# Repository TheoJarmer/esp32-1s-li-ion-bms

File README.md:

# ESP32 1S Li-ion BMS & Power Board

2-layer KiCad PCB that charges and protects a single Li-ion cell and
provides a regulated 3.3V rail for an ESP32.

## Features
- USB-C input, charging via TP4056 (R_PROG = 2 kOhm, about 600 mA from the datasheet formula, not measured)
- Cell protection (DW01A + FS8205A)
- Automatic USB/battery power-path switching (P-MOSFET Q2 + Schottky D4)
- 3.3V regulation (AP2112K-3.3)

## Power path
USB power feeds the 3.3V regulator through Schottky diode D4, and P-channel
MOSFET Q2 (gate tied to VBUS) connects the battery to the same node only when
USB is absent. D4 blocks current flowing back to the USB port.

## Testing done
- 3.3V output from USB power
- 3.3V output from battery power
- 3.3V output maintained when switching between USB and battery (unplugging each at different times)
- Battery charging

## Not tested
- Operation with an ESP32 connected
- Measured charge current
- Protection cutoffs (overcurrent, over-discharge, short circuit)
- Temperature sensing (TH1 replaced by a fixed 10 kOhm resistor on the built board)

## Files
- hardware/: KiCad project
- manufacturing/: gerbers, bom.csv, jlcpcb_order_bom.csv, placement file
- docs/: schematic PDF
- img/: photos and PCB render

## Build
5 boards fabricated by JLCPCB (SMD parts assembled by JLCPCB, through-hole parts hand-soldered).
Designed and simulated in KiCad 10.0.

## License
MIT

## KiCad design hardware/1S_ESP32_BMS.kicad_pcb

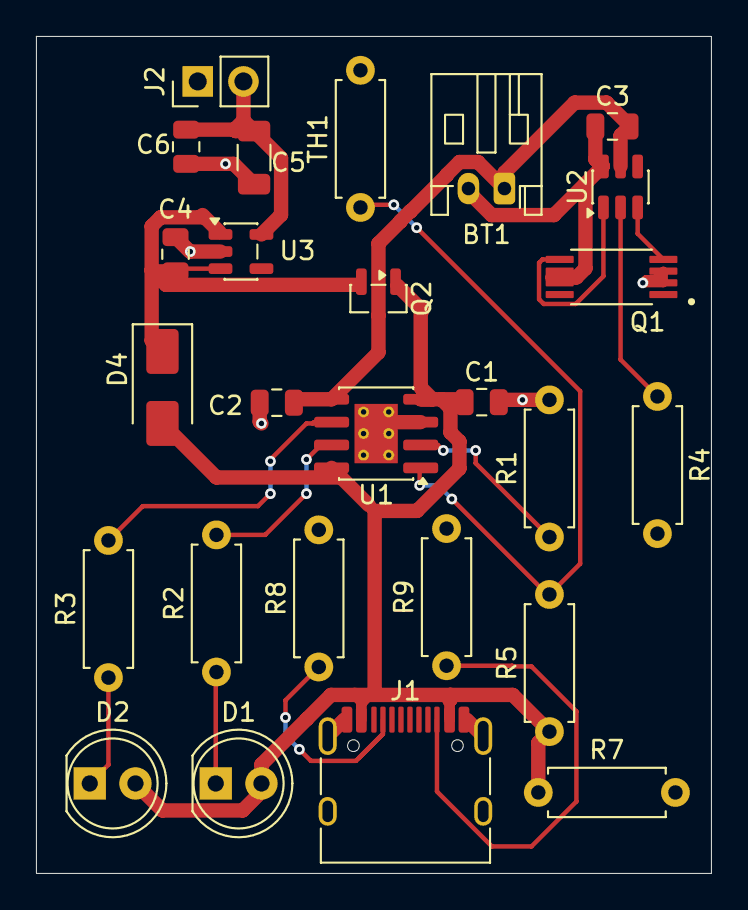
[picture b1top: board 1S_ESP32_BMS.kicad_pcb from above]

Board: 2 copper layers, 37.5 x 46.5 mm, 26 parts (0 on the bottom side), 17 nets.

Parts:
BT1: Battery_Cell; JST_PH_S2B-PH-K_1x02_P2.00mm_Horizontal
C1, C4: 10 uf; C_0805_2012Metric
C2: 10uf; C_0805_2012Metric
C3: 0.1uf; C_0805_2012Metric
C5: 22 uf; C_1206_3216Metric
C6: 0.1 uf; C_0805_2012Metric
D1: RED LED; LED_D5.0mm
D2: Green LED; LED_D5.0mm
D4: SS14; D_SMA
J1: USB_C_Receptacle_PowerOnly_24P; USB_C_Receptacle_HRO_TYPE-C-31-M-12
J2: Conn_01x02_Pin; PinHeader_1x02_P2.54mm_Vertical
Q1: FS8205A; SOP65P640X120-8N
Q2: AO3401A; SOT-23
R1: 4.7 kohm; R_Axial_DIN0207_L6.3mm_D2.5mm_P7.62mm_Horizontal
R2, R3, R4: 1kohm; R_Axial_DIN0207_L6.3mm_D2.5mm_P7.62mm_Horizontal
R5: 10 kmohm; R_Axial_DIN0207_L6.3mm_D2.5mm_P7.62mm_Horizontal
R7: 100 kmohm; R_Axial_DIN0207_L6.3mm_D2.5mm_P7.62mm_Horizontal
R8, R9: 5.1 kohm; R_Axial_DIN0207_L6.3mm_D2.5mm_P7.62mm_Horizontal
TH1: 10k ntc; R_Axial_DIN0207_L6.3mm_D2.5mm_P7.62mm_Horizontal
U1: TP4056-42-ESOP8; SOIC-8-1EP_3.9x4.9mm_P1.27mm_EP2.41x3.3mm_ThermalVias
U2: DW01A; SOT-23-6
U3: AP2112K-3.3; SOT-23-5

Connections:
Earth: C1.2, C2.1, C4.1, C5.1, C6.1, J1.A1 (GND), J1.A12 (GND), J1.B1 (GND), J1.B12 (GND), J1.SH (SHIELD), J2.1, Q1.2, Q1.3, R1.2, R4.2, R7.2, R8.2, R9.2, TH1.2, U1.3 (GND), U1.9 (EPAD), U3.2 (GND)
unnamed: BT1.1 (+), C2.2, C3.2, Q2.3 (D), U1.5 (BAT), U2.5 (VCC)
unnamed: BT1.2 (-), C3.1, Q1.6, Q1.7, U2.6 (GND)
unnamed: C1.1, D1.2 (A), D2.2 (A), D4.2 (A), J1.A4 (VBUS), J1.A9 (VBUS), J1.B4 (VBUS), J1.B9 (VBUS), Q2.1 (G), R5.1, R7.1, U1.4 (V_{CC}), U1.8 (CE)
unnamed: D1.1 (K), R2.1
unnamed: D2.1 (K), R3.1
unnamed: C4.2, D4.1 (K), Q2.2 (S), U3.1 (VIN), U3.3 (EN)
unnamed: J1.A5 (CC1), R8.1
unnamed: J1.B5 (CC2), R9.1
unnamed: C5.2, C6.2, J2.2, U3.5 (VOUT)
unnamed: R1.1, U1.2 (PROG)
unnamed: R5.2, TH1.1, U1.1 (TEMP)
unnamed: R2.2, U1.7 (~CHRG)
unnamed: R3.2, U1.6 (~STDBY)
unnamed: R4.1, U2.2 (CS)
unnamed: Q1.4, U2.3 (OC)
unnamed: Q1.5, U2.1 (OD)
